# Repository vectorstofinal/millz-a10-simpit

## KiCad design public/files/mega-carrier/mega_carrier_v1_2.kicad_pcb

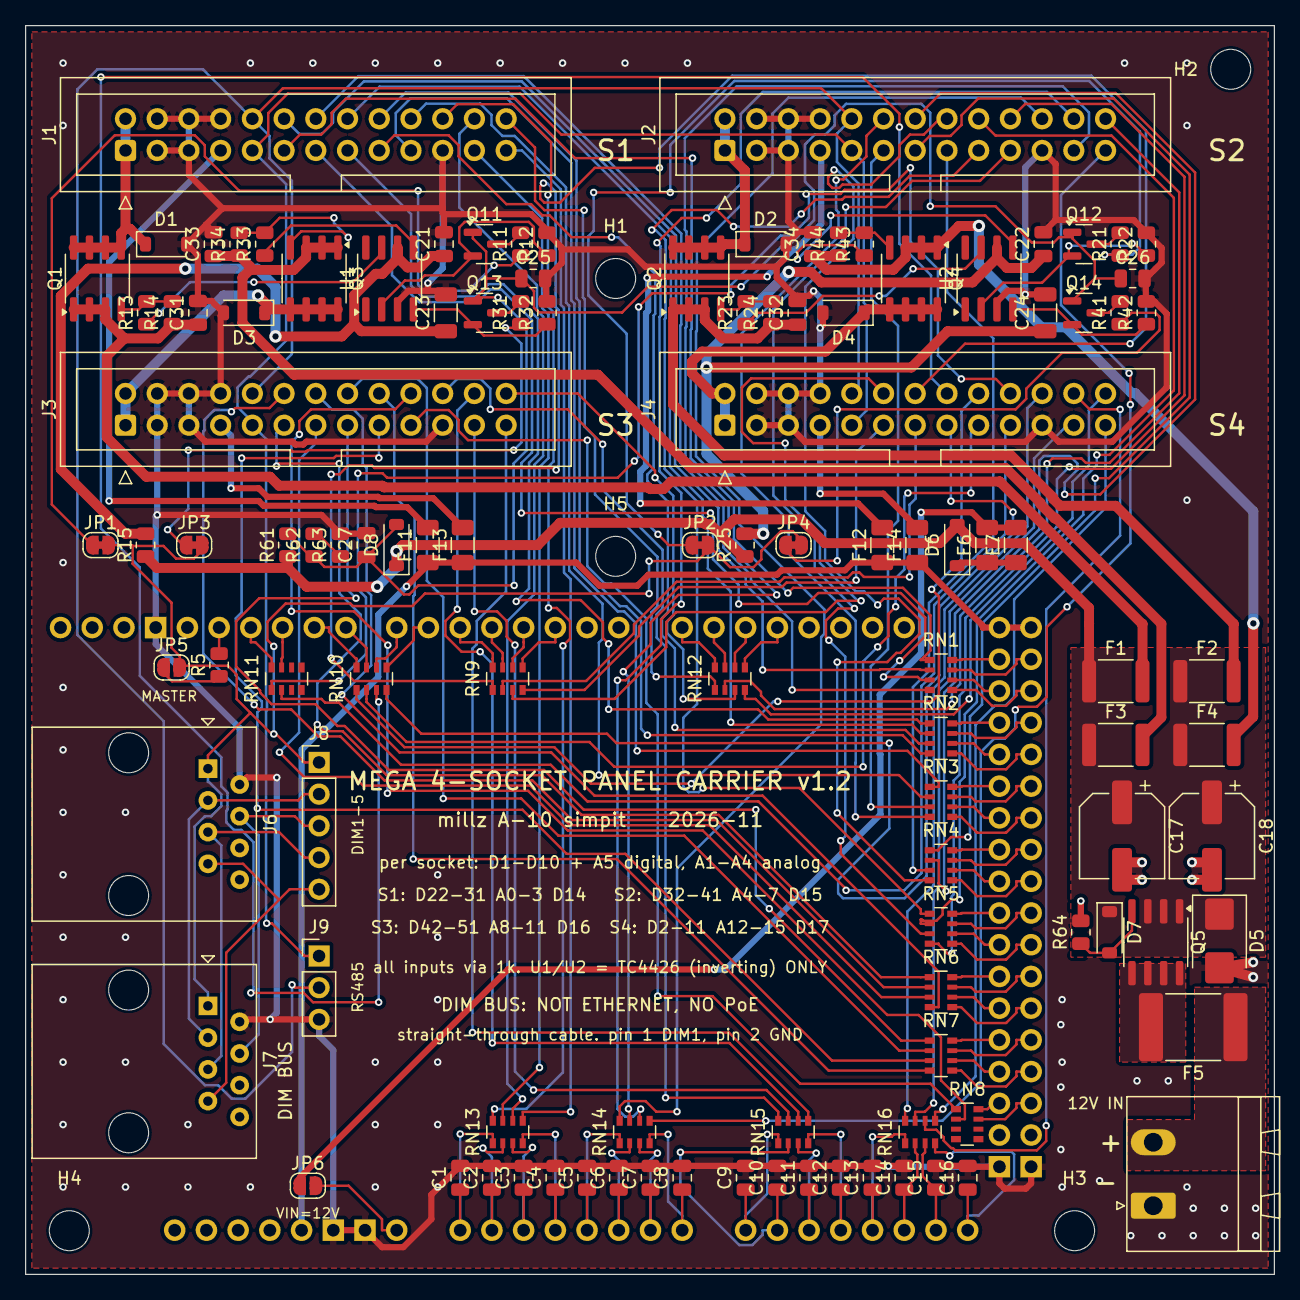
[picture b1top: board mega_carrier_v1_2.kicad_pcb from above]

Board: 2 copper layers, 100.0 x 100.0 mm, 119 parts (0 on the bottom side), 174 nets.

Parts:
A1: Mega 2560 headers (hand-fit, bottom); Arduino_Mega2560_R3_Shield
C1, C2, C3, C4, C5, C6, C7, C8, C9, C10, C11, C12, C13, C14, C15, C16, C21, C22, C25, C26, C27, C31, C32, C33, C34: 100nF; C_0805_2012Metric
C17, C18: 220uF 25V; CP_Elec_6.3x7.7
C23, C24: 10uF 50V; C_1206_3216Metric
D1, D2, D3, D4, D6, D8: B5819W; D_SOD-123
D5: SMBJ13A; D_SMB
D7: BZT52C15; D_SOD-123
F1, F2, F3, F4: PPTC 1.5A 24V; Fuse_1812_4532Metric
F5: PPTC 5A 24V; Fuse_2920_7451Metric
F6, F7, F11, F12, F13, F14: PPTC 0.1A 60V; Fuse_1206_3216Metric
H1, H2, H3, H4, H5: M3; MountingHole_3.2mm_M3
J1: Panel socket S1; IDC-Header_2x13_P2.54mm_Vertical
J2: Panel socket S2; IDC-Header_2x13_P2.54mm_Vertical
J3: Panel socket S3; IDC-Header_2x13_P2.54mm_Vertical
J4: Panel socket S4; IDC-Header_2x13_P2.54mm_Vertical
J5: 12V IN; PhoenixContact_MSTBA_2,5_2-G-5,08_1x02_P5.08mm_Horizontal
J6, J7: DIM BUS (RJ45); RJ45_Amphenol_54602-x08_Horizontal
J8: DIM TAP 1-5 (not fitted); PinHeader_1x05_P2.54mm_Vertical
J9: RS-485 A/B/GND (not fitted); PinHeader_1x03_P2.54mm_Vertical
JP1, JP2, JP3, JP4: DIM1 (cut to regroup); SolderJumper-2_P1.3mm_Bridged_RoundedPad1.0x1.5mm
JP5: MASTER (bridge on the dim-master PCB only); SolderJumper-2_P1.3mm_Open_RoundedPad1.0x1.5mm
JP6: VIN FROM 12V (normally open); SolderJumper-2_P1.3mm_Open_RoundedPad1.0x1.5mm
Q1, Q2, Q3, Q4, Q5: AO4407A; SOIC-8_3.9x4.9mm_P1.27mm
Q11, Q12, Q13, Q14: 2N7002; SOT-23
R5: 220R; R_0805_2012Metric
R11, R21, R31, R41: 2.2k; R_0805_2012Metric
R12, R14, R22, R24, R32, R34, R42, R44, R61, R62, R63, R64: 100k; R_0805_2012Metric
R13, R23, R33, R43: 100R; R_0805_2012Metric
R15, R25: 10R; R_0805_2012Metric
RN1, RN2, RN3, RN4, RN5, RN6, RN7, RN8, RN9, RN10, RN11, RN12, RN13, RN14, RN15, RN16: 4x 1k; R_Array_Convex_4x0603
U1, U2: TC4426; SOIC-8_3.9x4.9mm_P1.27mm

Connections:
+5V: A1.5V1, A1.5V3, A1.5V4, F11.1, F12.1, F13.1, F14.1
+12V: C17.1, C18.1, D5.1, D6.2, D7.1, D8.1, F1.1, F2.1, F3.1, F4.1, Q5.1, Q5.2, Q5.3, R15.1, R25.1, R61.1
A0: A1.A0, C1.1, RN13.1
A1: A1.A1, C2.1, RN13.2
A2: A1.A2, C3.1, RN13.3
A3: A1.A3, C4.1, RN13.4
A4: A1.A4, C5.1, RN14.1
A5: A1.A5, C6.1, RN14.2
A6: A1.A6, C7.1, RN14.3
A7: A1.A7, C8.1, RN14.4
A8: A1.A8, C9.1, RN15.1
A9: A1.A9, C10.1, RN15.2
A10: A1.A10, C11.1, RN15.3
A11: A1.A11, C12.1, RN15.4
A12: A1.A12, C13.1, RN16.1
A13: A1.A13, C14.1, RN16.2
A14: A1.A14, C15.1, RN16.3
A15: A1.A15, C16.1, RN16.4
BUS_A: J1.9, J2.9, J3.9, J4.9, J9.1
BUS_B: J1.10, J2.10, J3.10, J4.10, J9.2
D2: A1.D2, RN9.5
D3: A1.D3, RN9.6
D4: A1.D4, RN9.7
D5: A1.D5, RN9.8
D6: A1.D6, RN10.5
D7: A1.D7, RN10.6
D8: A1.D8, RN10.7
D9: A1.D9, RN10.8
D10: A1.D10, RN11.7
D11: A1.D11, RN11.8
D12: A1.D12, R5.2
D14: A1.D14, RN12.8
D15: A1.D15, RN12.7
D16: A1.D16, RN12.6
D17: A1.D17, RN12.5
D22: A1.D22, RN1.8
D23: A1.D23, RN1.7
D24: A1.D24, RN1.6
D25: A1.D25, RN1.5
D26: A1.D26, RN2.8
D27: A1.D27, RN2.7
D28: A1.D28, RN2.6
D29: A1.D29, RN2.5
D30: A1.D30, RN3.8
D31: A1.D31, RN3.7
D32: A1.D32, RN3.6
D33: A1.D33, RN3.5
D34: A1.D34, RN4.8
D35: A1.D35, RN4.7
D36: A1.D36, RN4.6
D37: A1.D37, RN4.5
D38: A1.D38, RN5.8
D39: A1.D39, RN5.7
D40: A1.D40, RN5.6
D41: A1.D41, RN5.5
D42: A1.D42, RN6.8
D43: A1.D43, RN6.7
D44: A1.D44, RN6.6
D45: A1.D45, RN6.5
D46: A1.D46, RN7.8
D47: A1.D47, RN7.7
D48: A1.D48, RN7.6
D49: A1.D49, RN7.5
D50: A1.D50, RN8.8
D51: A1.D51, RN8.7
DIM1: J6.1, J7.1, J8.1, JP1.2, JP2.2, JP3.2, JP4.2, JP5.2
DIM2: J6.3, J7.3, J8.2
DIM3: J6.4, J7.4, J8.3
DIM4: J6.5, J7.5, J8.4
DIM5: J6.7, J7.7, J8.5
DPASS1: Q11.3, R11.2
DPASS2: Q12.3, R21.2
DPASS3: Q13.3, R31.2
DPASS4: Q14.3, R41.2
DRVIN1: Q11.2, R12.1, U1.2
DRVIN2: Q12.2, R22.1, U2.2
DRVIN3: Q13.2, R32.1, U1.4
DRVIN4: Q14.2, R42.1, U2.4
DSEL1: JP1.1, R11.1
DSEL2: JP2.1, R21.1
DSEL3: JP3.1, R31.1
DSEL4: JP4.1, R41.1
FUSED1: C31.1, F1.2, Q1.1, Q1.2, Q1.3, R14.1
FUSED2: C32.1, F2.2, Q2.1, Q2.2, Q2.3, R24.1
FUSED3: C33.1, F3.2, Q3.1, Q3.2, Q3.3, R34.1
FUSED4: C34.1, F4.2, Q4.1, Q4.2, Q4.3, R44.1
GDRV1: R13.1, U1.7
GDRV2: R23.1, U2.7
GDRV3: R33.1, U1.5
GDRV4: R43.1, U2.5
GND: A1.GND1, A1.GND2, A1.GND3, A1.GND5, A1.GND6, C1.2, C2.2, C3.2, C4.2, C5.2, C6.2, C7.2, C8.2, C9.2, C10.2, C11.2, C12.2, C13.2, C14.2, C15.2, C16.2, C17.2, C18.2, C21.2, C22.2, C23.2, C24.2, C25.2, C26.2, C27.2, C31.2, C32.2, C33.2, C34.2, D1.2, D2.2, D3.2, D4.2, D5.2, J1.3, J1.4, J1.5, J1.6, J1.8, J1.21, J2.3, J2.4, J2.5, J2.6, J2.8, J2.21, J3.3, J3.4, J3.5, J3.6, J3.8, J3.21, J4.3, J4.4, J4.5, J4.6, J4.8, J4.21, J5.1, J6.2, J7.2, J9.3, R12.2, R22.2, R32.2, R42.2, R63.2, R64.2, U1.3, U2.3
LEDP1: D1.1, J1.1, J1.2, Q1.5, Q1.6, Q1.7, Q1.8
LEDP2: D2.1, J2.1, J2.2, Q2.5, Q2.6, Q2.7, Q2.8
LEDP3: D3.1, J3.1, J3.2, Q3.5, Q3.6, Q3.7, Q3.8
LEDP4: D4.1, J4.1, J4.2, Q4.5, Q4.6, Q4.7, Q4.8
MPWM: JP5.1, R5.1
P5V1: F11.2, J1.7
P5V2: F12.2, J2.7
P5V3: F13.2, J3.7
P5V4: F14.2, J4.7
PGATE1: Q1.4, R13.2, R14.2
PGATE2: Q2.4, R23.2, R24.2
PGATE3: Q3.4, R33.2, R34.2
PGATE4: Q4.4, R43.2, R44.2
RPG: D7.2, Q5.4, R64.1
S_A0: J1.22, RN13.8
S_A1: J1.23, RN13.7
S_A2: J1.24, RN13.6
S_A3: J1.25, RN13.5
S_A4: J2.22, RN14.8
S_A5: J2.23, RN14.7
S_A6: J2.24, RN14.6
S_A7: J2.25, RN14.5
S_A8: J3.22, RN15.8
S_A9: J3.23, RN15.7
S_A10: J3.24, RN15.6
S_A11: J3.25, RN15.5
S_A12: J4.22, RN16.8
S_A13: J4.23, RN16.7
S_A14: J4.24, RN16.6
S_A15: J4.25, RN16.5
S_D2: J4.11, RN9.4
S_D3: J4.12, RN9.3
S_D4: J4.13, RN9.2
S_D5: J4.14, RN9.1
S_D6: J4.15, RN10.4
S_D7: J4.16, RN10.3
S_D8: J4.17, RN10.2
S_D9: J4.18, RN10.1
S_D10: J4.19, RN11.2
S_D11: J4.20, RN11.1
S_D14: J1.26, RN12.1
S_D15: J2.26, RN12.2
S_D16: J3.26, RN12.3
S_D17: J4.26, RN12.4
S_D22: J1.11, RN1.1
S_D23: J1.12, RN1.2
S_D24: J1.13, RN1.3
S_D25: J1.14, RN1.4
S_D26: J1.15, RN2.1
S_D27: J1.16, RN2.2
S_D28: J1.17, RN2.3
S_D29: J1.18, RN2.4
S_D30: J1.19, RN3.1
S_D31: J1.20, RN3.2
S_D32: J2.11, RN3.3
S_D33: J2.12, RN3.4
S_D34: J2.13, RN4.1
S_D35: J2.14, RN4.2
S_D36: J2.15, RN4.3
S_D37: J2.16, RN4.4
S_D38: J2.17, RN5.1
S_D39: J2.18, RN5.2
S_D40: J2.19, RN5.3
S_D41: J2.20, RN5.4
S_D42: J3.11, RN6.1
S_D43: J3.12, RN6.2
S_D44: J3.13, RN6.3
S_D45: J3.14, RN6.4
S_D46: J3.15, RN7.1
S_D47: J3.16, RN7.2
S_D48: J3.17, RN7.3
S_D49: J3.18, RN7.4
S_D50: J3.19, RN8.1
S_D51: J3.20, RN8.2
VD6: D6.1, F6.1, F7.1
VDRV1: C21.1, C23.1, R15.2, U1.6
VDRV2: C22.1, C24.1, R25.2, U2.6
VIN: A1.VIN, JP6.2
VINF: F5.2, Q5.5, Q5.6, Q5.7, Q5.8
VINJ: F6.2, F7.2, JP6.1
VPASS: C25.1, C26.1, C27.1, D8.2, Q11.1, Q12.1, Q13.1, Q14.1, R61.2, R62.1
VPM: R62.2, R63.1
VRAW: F5.1, J5.2

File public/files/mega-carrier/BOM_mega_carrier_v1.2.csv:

Comment,Designator,Footprint,LCSC Part #
100nF 50V X7R 0805,"C1,C2,C3,C4,C5,C6,C7,C8,C9,C10,C11,C12,C13,C14,C15,C16,C21,C22,C25,C26,C27,C31,C32,C33,C34",C_0805_2012Metric,C49678
220uF 25V electrolytic SMD 6.3x7.7 (EEE-FTE221XAL),"C17,C18",CP_Elec_6.3x7.7,C1881633
10uF 50V X5R 1206,"C23,C24",C_1206_3216Metric,C13585
B5819W Schottky 40V 1A SOD-123,"D1,D2,D3,D4,D6,D8",D_SOD-123,C8598
SMBJ13A TVS 13V unidirectional SMB,D5,D_SMB,C353394
BZT52C15 Zener 15V SOD-123,D7,D_SOD-123,C2104
PPTC resettable fuse 1.5A hold 24V 1812 (mSMD150-24V),"F1,F2,F3,F4",Fuse_1812_4532Metric,C70123
PPTC resettable fuse 5A hold 24V 2920 (2920L500/24SLDR),F5,Fuse_2920_7451Metric,C1512058
PPTC resettable fuse 0.1A hold 60V 1206 (SMD1206P010TF),"F6,F7,F11,F12,F13,F14",Fuse_1206_3216Metric,C20981
2x13 box header 2.54mm straight no-ejector DC3-2.54-26PAS (panel socket),"J1,J2,J3,J4",IDC-Header_2x13_P2.54mm_Vertical,C5156668
Pluggable terminal block header 2P 5.08mm right-angle WJ2EDGRC-5.08-02P (12V in),J5,"PhoenixContact_MSTBA_2,5_2-G-5,08_1x02_P5.08mm_Horizontal",C3697
AO4407A P-MOSFET 30V SOIC-8,"Q1,Q2,Q3,Q4,Q5",SOIC-8_3.9x4.9mm_P1.27mm,C16072
2N7002 N-MOSFET SOT-23,"Q11,Q12,Q13,Q14",SOT-23,C8545
220R 0805,R5,R_0805_2012Metric,C17557
2.2k 0805,"R11,R21,R31,R41",R_0805_2012Metric,C17520
100k 0805,"R12,R14,R22,R24,R32,R34,R42,R44,R61,R62,R63,R64",R_0805_2012Metric,C149504
100R 0805,"R13,R23,R33,R43",R_0805_2012Metric,C17408
10R 0805,"R15,R25",R_0805_2012Metric,C17415
1k x4 resistor array 0603x4 (4D03WGJ0102T5E),"RN1,RN2,RN3,RN4,RN5,RN6,RN7,RN8,RN9,RN10,RN11,RN12,RN13,RN14,RN15,RN16",R_Array_Convex_4x0603,C20197
TC4426 dual inverting gate driver SOIC-8,"U1,U2",SOIC-8_3.9x4.9mm_P1.27mm,C27201
